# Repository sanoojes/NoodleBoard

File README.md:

# NoodleBoard

A simple Development Board using RP2040 created by following the
[Guide](https://blueprint.hackclub.com/starter-projects/devboard) and adding
some personal magic

## PCB

Images of PCB

## BOM (Bill of materials)

| Qty     | Item                     | Desc            | Size               | Link                                                                                                  |
| ------- | ------------------------ | --------------- | ------------------ | ----------------------------------------------------------------------------------------------------- |
| 11x     | 0.1uF(100nF)             | Capacitor       | 0402(1005Metric)   | Link                                                                                                  |
| 2x      | 1uF(1000nF)              | Capacitor       | 0402(1005Metric)   | Link                                                                                                  |
| 2x      | 10uF                     | Capacitor       | 0603(1608Metric)   | Link                                                                                                  |
| 2x      | 33pF                     | Capacitor       | 0402(1005Metric)   | Link                                                                                                  |
| 4x      | 1k Ohm                   | Resistor        | 0402(1005Metric)   | Link                                                                                                  |
| 2x      | 5.1k Ohm                 | Resistor        | 0603(1608Metric)   | Link                                                                                                  |
| 2x      | 27 Ohm                   | Resistor        | 0402(1005Metric)   | Link                                                                                                  |
| 2x      | 10k Ohm                  | Resistor        | 0603(1608Metric)   | Link                                                                                                  |
| 2x      | 16-213SDRC/S530-A3/TR8   | Red LED         | 0402(1005Metric)   | [Link](https://jlcpcb.com/partdetail/EverlightElec-16_213SDRC_S530_A3TR8/C71911)                      |
| 1x      | RP2040                   | Microcontroller | QFN-56-1EP         | [Link](https://jlcpcb.com/partdetail/RaspberryPi-RP2040/C2040)                                        |
| 1x      | ME6211C33M5G-N           | LDO Regulator   | SOT-23-5           | [Link](https://jlcpcb.com/partdetail/84106-ME6211C33M5GN/C82942)                                      |
| 1x      | W25Q16JVZPIQ             | Flash           | Winbond_USON-8-1EP | [Link](https://jlcpcb.com/partdetail/WinbondElec-W25Q16JVZPIQ/C377853)                                |
| 1x      | 12MHz                    | Crystal         | 3225 4Pin          | [Link](https://jlcpcb.com/partdetail/YXC_CrystalOscillators-X322512MSB4SI/C9002)                      |
| 2x      | TS-1088-AR02016          | Switches        | SPST_NO_Alps_SKRK  | [Link](https://jlcpcb.com/partdetail/XUNPU-TS_1088AR02016/C720477)                                    |
| 1x      | USBC Female              | USBC Connector  | TYPE-C-31-M-12     | [Link](https://jlcpcb.com/partdetail/Korean_HropartsElec-TYPE_C_31_M12/C165948)                       |
| 46 (1x) | Pin Header Vertical Male | Pin Headers     | 2.54mm             | [Link](https://robu.in/product/2-54mm-1x40-pin-male-single-row-straight-long-header-strip-pack-of-3/) |

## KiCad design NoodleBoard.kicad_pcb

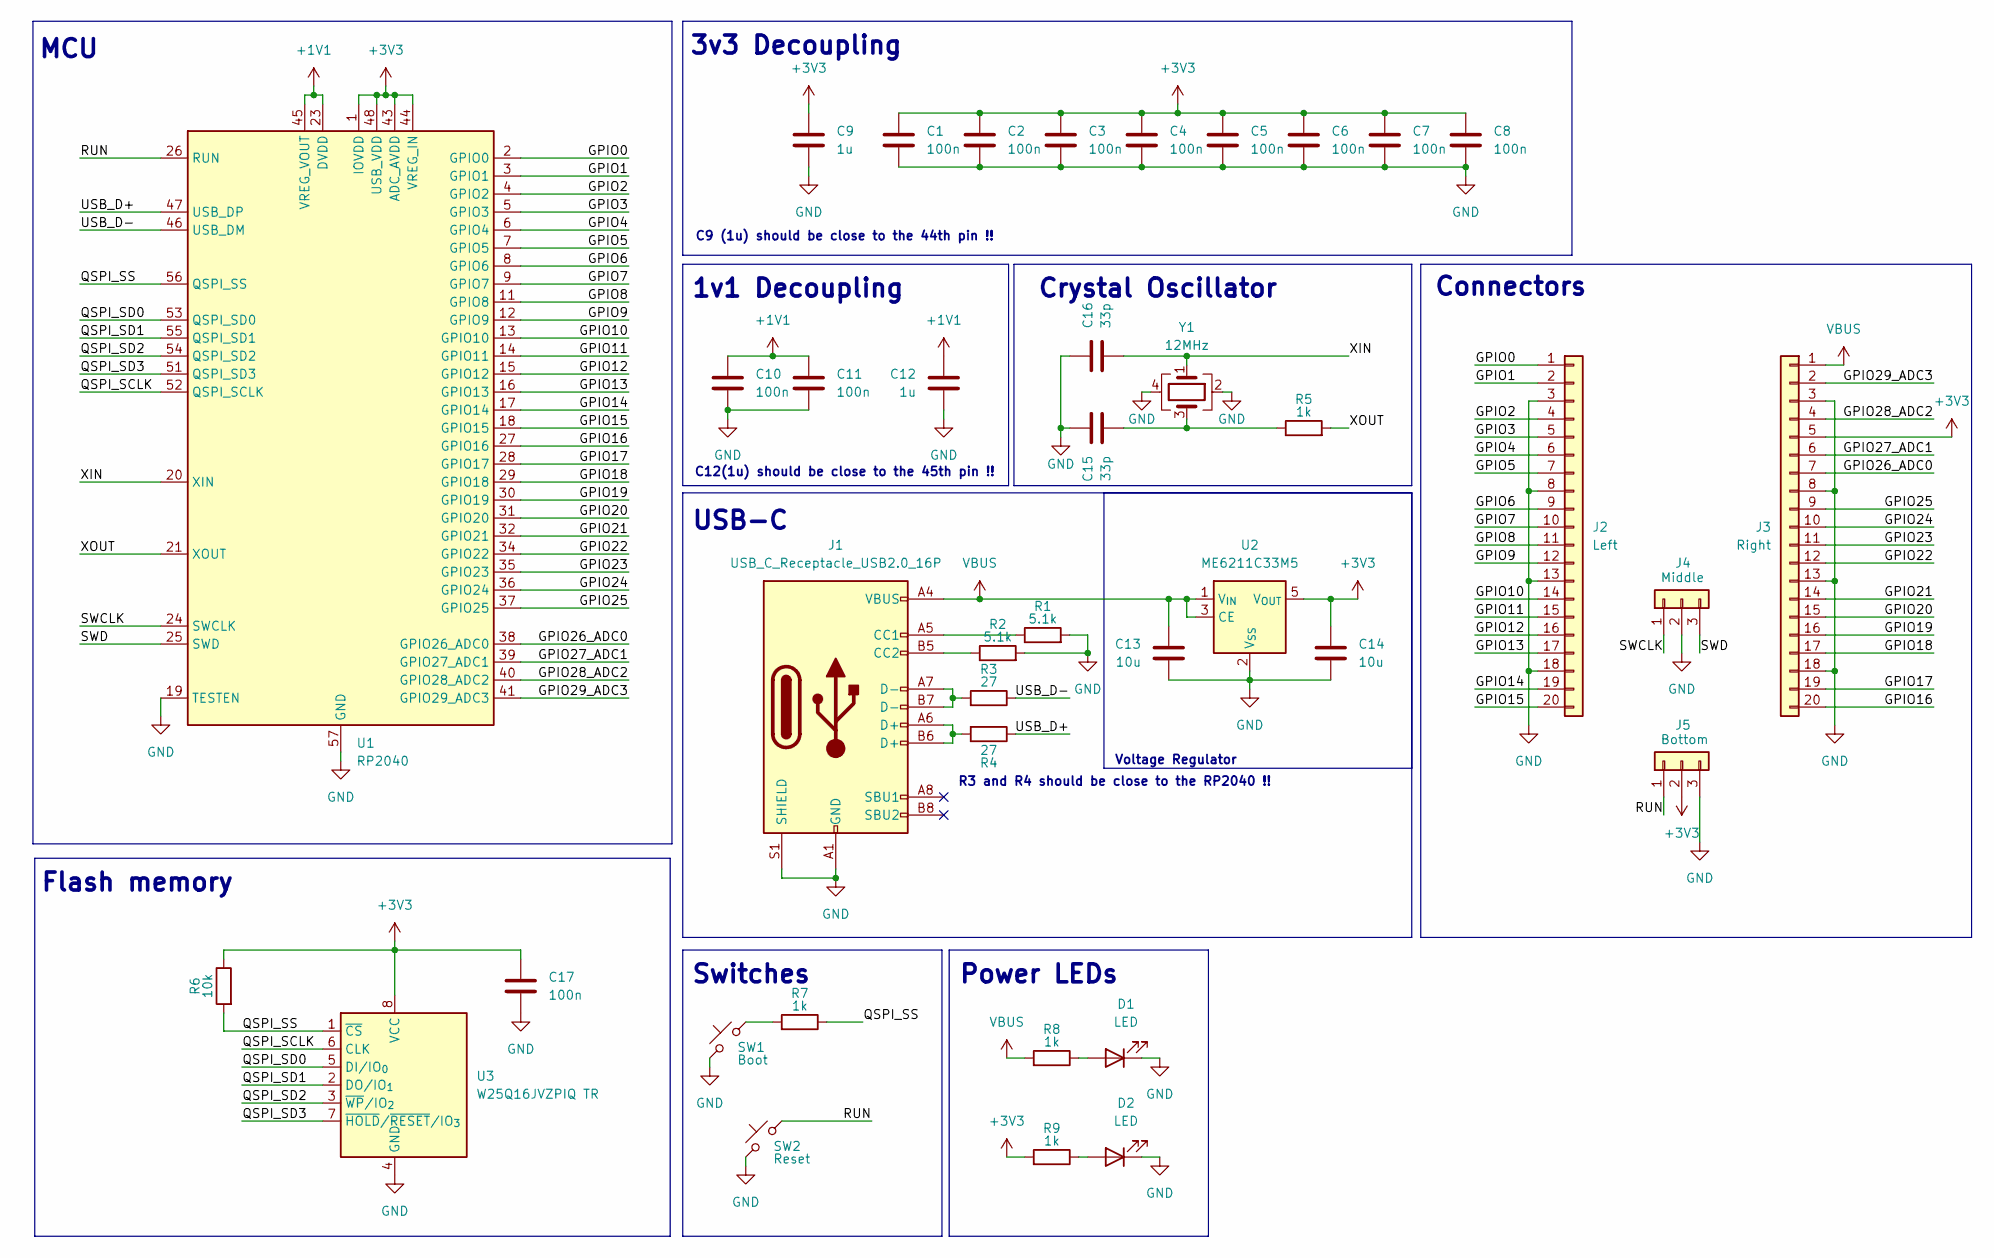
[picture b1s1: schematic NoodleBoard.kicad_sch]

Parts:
C1, C2, C3, C4, C5, C6, C7, C8, C10, C11, C17: 100n; C_0402_1005Metric
C9, C12: 1u; C_0402_1005Metric
C13, C14: 10u; C_0603_1608Metric
C15, C16: 33p; C_0402_1005Metric
D1, D2: LED; LED_0402_1005Metric
J1: USB_C_Receptacle_USB2.0_16P; USB_C_Receptacle_HRO_TYPE-C-31-M-12
J2: Left; PinHeader_1x20_P2.54mm_Vertical
J3: Right; PinHeader_1x20_P2.54mm_Vertical
J4: Middle; PinHeader_1x03_P2.54mm_Vertical
J5: Bottom; PinHeader_1x03_P2.54mm_Vertical
R1, R2: 5.1k; R_0603_1608Metric
R3, R4: 27; R_0402_1005Metric
R5, R7, R8, R9: 1k; R_0402_1005Metric
R6: 10k; R_0603_1608Metric
SW1: Boot; SW_Push_SPST_NO_Alps_SKRK
SW2: Reset; SW_Push_SPST_NO_Alps_SKRK
U1: RP2040; QFN-56-1EP_7x7mm_P0.4mm_EP3.2x3.2mm
U2: ME6211C33M5; SOT-23-5
U3: W25Q16JVZPIQ TR; Winbond_USON-8-1EP_3x2mm_P0.5mm_EP0.2x1.6mm
Y1: 12MHz; Crystal_SMD_3225-4Pin_3.2x2.5mm_HandSoldering

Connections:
+1V1: C10.1, C11.1, C12.2, U1.23 (DVDD), U1.45 (VREG_VOUT), U1.50 (DVDD)
+3V3: C1.1, C2.1, C3.1, C4.1, C5.1, C6.1, C7.1, C8.1, C9.2, C14.2, C17.1, J3.5, J5.2, R6.1, R9.2, U1.1 (IOVDD), U1.10 (IOVDD), U1.22 (IOVDD), U1.33 (IOVDD), U1.42 (IOVDD), U1.43 (ADC_AVDD), U1.44 (VREG_IN), U1.48 (USB_VDD), U1.49 (IOVDD), U2.5 (V_{OUT}), U3.8 (VCC)
/GPIO0: J2.1, U1.2 (GPIO0)
/GPIO1: J2.2, U1.3 (GPIO1)
/GPIO2: J2.4, U1.4 (GPIO2)
/GPIO3: J2.5, U1.5 (GPIO3)
/GPIO4: J2.6, U1.6 (GPIO4)
/GPIO5: J2.7, U1.7 (GPIO5)
/GPIO6: J2.9, U1.8 (GPIO6)
/GPIO7: J2.10, U1.9 (GPIO7)
/GPIO8: J2.11, U1.11 (GPIO8)
/GPIO9: J2.12, U1.12 (GPIO9)
/GPIO10: J2.14, U1.13 (GPIO10)
/GPIO11: J2.15, U1.14 (GPIO11)
/GPIO12: J2.16, U1.15 (GPIO12)
/GPIO13: J2.17, U1.16 (GPIO13)
/GPIO14: J2.19, U1.17 (GPIO14)
/GPIO15: J2.20, U1.18 (GPIO15)
/GPIO16: J3.20, U1.27 (GPIO16)
/GPIO17: J3.19, U1.28 (GPIO17)
/GPIO18: J3.17, U1.29 (GPIO18)
/GPIO19: J3.16, U1.30 (GPIO19)
/GPIO20: J3.15, U1.31 (GPIO20)
/GPIO21: J3.14, U1.32 (GPIO21)
/GPIO22: J3.12, U1.34 (GPIO22)
/GPIO23: J3.11, U1.35 (GPIO23)
/GPIO24: J3.10, U1.36 (GPIO24)
/GPIO25: J3.9, U1.37 (GPIO25)
/GPIO26_ADC0: J3.7, U1.38 (GPIO26_ADC0)
/GPIO27_ADC1: J3.6, U1.39 (GPIO27_ADC1)
/GPIO28_ADC2: J3.4, U1.40 (GPIO28_ADC2)
/GPIO29_ADC3: J3.2, U1.41 (GPIO29_ADC3)
/QSPI_SCLK: U1.52 (QSPI_SCLK), U3.6 (CLK)
/QSPI_SD0: U1.53 (QSPI_SD0), U3.5 (DI/IO_{0})
/QSPI_SD1: U1.55 (QSPI_SD1), U3.2 (DO/IO_{1})
/QSPI_SD2: U1.54 (QSPI_SD2), U3.3 (~WP/IO_{2})
/QSPI_SD3: U1.51 (QSPI_SD3), U3.7 (~HOLD/~RESET/IO_{3})
/QSPI_SS: R6.2, R7.1, U1.56 (QSPI_SS), U3.1 (~CS)
/RUN: J5.1, SW2.2, U1.26 (RUN)
/SWCLK: J4.1, U1.24 (SWCLK)
/SWD: J4.3, U1.25 (SWD)
/USB_D+: R4.1, U1.47 (USB_DP)
/USB_D-: R3.1, U1.46 (USB_DM)
/XIN: C16.2, U1.20 (XIN), Y1.1
/XOUT: R5.2, U1.21 (XOUT)
GND: C1.2, C2.2, C3.2, C4.2, C5.2, C6.2, C7.2, C8.2, C9.1, C10.2, C11.2, C12.1, C13.1, C14.1, C15.1, C16.1, C17.2, D1.1 (K), D2.1 (K), J1.A1 (GND), J1.A12 (GND), J1.B1 (GND), J1.B12 (GND), J1.S1 (SHIELD), J2.3, J2.8, J2.13, J2.18, J3.3, J3.8, J3.13, J3.18, J4.2, J5.3, R1.2, R2.2, SW1.1, SW2.1, U1.19 (TESTEN), U1.57 (GND), U2.2 (V_{SS}), U3.4 (GND), Y1.2, Y1.4
unnamed: C15.2, R5.1, Y1.3
unnamed: D1.2 (A), R8.1
unnamed: D2.2 (A), R9.1
unnamed: J1.A5 (CC1), R1.1
unnamed: J1.B5 (CC2), R2.1
unnamed: J1.A6 (D+), J1.B6 (D+), R4.2
unnamed: J1.A7 (D-), J1.B7 (D-), R3.2
unnamed: R7.2, SW1.2
VBUS: C13.2, J1.A4 (VBUS), J1.A9 (VBUS), J1.B4 (VBUS), J1.B9 (VBUS), J3.1, R8.2, U2.1 (V_{IN}), U2.3 (CE)

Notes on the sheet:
Power LEDs
Connectors
Flash memory
MCU
3v3 Decoupling
C12(1u) should be close to the 45th pin !!
USB-C
Switches
1v1 Decoupling
Voltage Regulator
R3 and R4 should be close to the RP2040 !!
C9 (1u) should be close to the 44th pin !!
Crystal Oscillator

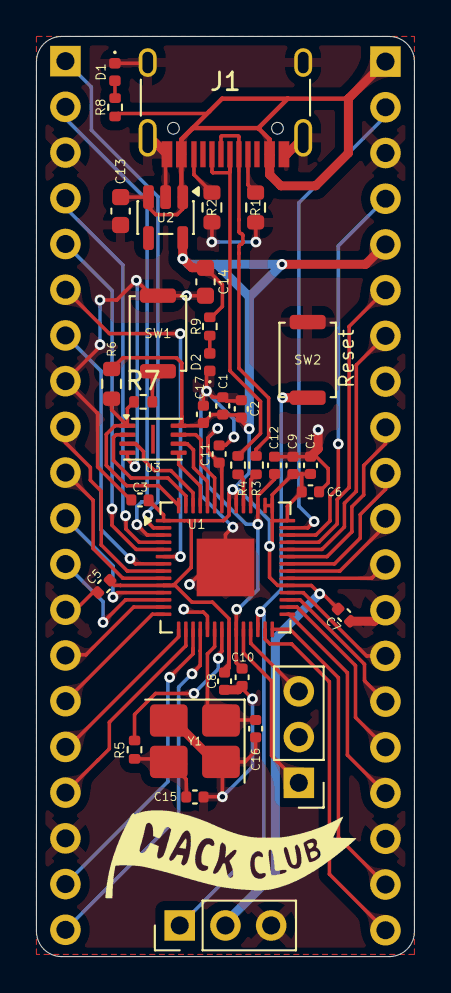
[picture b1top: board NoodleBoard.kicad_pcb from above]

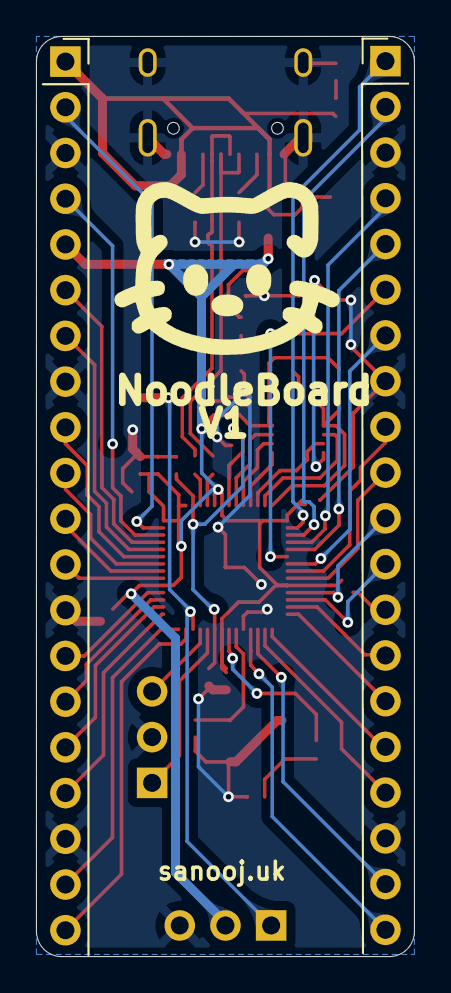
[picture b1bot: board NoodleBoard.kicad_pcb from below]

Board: 2 copper layers, 21.0 x 51.1 mm, 39 parts (2 on the bottom side), 55 nets.

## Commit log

2025-12-30 feat: setup schematics
2026-01-01 feat: upload v1 pcb and schematics
2026-01-01 feat: add all the files
2026-01-01 fix: robu link
2026-01-08 make pcb a bit better
